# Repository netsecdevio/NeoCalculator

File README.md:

<div align="center">

<br>

# 🔢 NumOS

### Open-Source Scientific Graphing Calculator OS

**ESP32-S3 N16R8 · ILI9341 IPS 320×240 · LVGL 9.x · CAS Engine · Natural Display V.P.A.M.**

<br>

**[🚀 Join the Hardware Waitlist here](https://neocalculator.tech)** to get notified when PCB beta units drop.

---

</div>

> **Youth Hacking 4 Freedom 2026 submission:** see [`YH4F_SUBMISSION.md`](YH4F_SUBMISSION.md).
>
> **Demo video:** [youtu.be/IOTeKleOHQY](https://youtu.be/IOTeKleOHQY) — launcher, Calculation, natural-display math, and Grapher.

## Table of Contents

0. [Webpage](https://neocalculator.tech/)
1. [What is NumOS?](#what-is-numos)
2. [Key Features](#key-features)
3. [Photo Gallery](#photo-gallery)
4. [System Architecture](#system-architecture)
5. [CAS Engine](#CAS-engine)
6. [Hardware](#hardware)
7. [Quick Start](#quick-start)
8. [User Manual — EquationsApp](#user-manual--equationsapp)
9. [Project Structure](#project-structure)
10. [Build Stats](#build-stats)
11. [Critical Hardware Fixes](#critical-hardware-fixes)
12. [Project Status](#project-status)
13. [Technology Stack](#technology-stack)
14. [Comparison with Commercial Calculators](#comparison-with-commercial-calculators)
15. [Documentation](#documentation)
16. [Contributing](#contributing)

---

## What is NumOS?

**NumOS** is an open-source scientific and graphing calculator operating system built on the **ESP32-S3 N16R8** microcontroller (16 MB QIO runtime flash, DIO ROM boot header + 8 MB PSRAM OPI). The project aims to provide advanced features comparable to established scientific calculators, including symbolic mathematics, graphing, and natural display formatting.

*Working toward delivering a capable CAS experience for a ~€20 BOM as an open-source alternative in the educational calculator space.*

**NumOS delivers:**

- **Giac-backed CAS Engine** — Symbolic math implementation using Giac C++ via `src/math/giac/GiacBridge.cpp` for evaluation. Legacy CAS-S3 modules remain documented as historical milestones and optional local tooling.
- **Natural Display V.P.A.M.** — Formulae rendered as they appear on paper: real stacked fractions, radical symbols (√), genuine superscripts, 2D navigation with a structural smart cursor.
 - **Modern LVGL 9.x Interface** — Smooth transitions, animated splash screen, NumWorks-style launcher.
    Recent launcher refactor: the launcher now uses LVGL Flex `ROW_WRAP` (dynamic rows) with fixed card sizing
    instead of a static grid descriptor. See `docs/UI_CHANGES.md` for developer migration notes and
    `docs/fluid2d_plan.md` for an example app (Fluid2D) integrated into the new APPS[] schema.
- **Custom Numeric Math Engine** — Complete pipeline: Tokenizer → Shunting-Yard Parser → RPN Evaluator + Visual AST, implemented from scratch in C++17.
- **Modular App Architecture** — Each application is a self-contained module with explicit lifecycle (`begin/end/load/handleKey`), orchestrated by `SystemApp`.

---

## Key Features

| Feature | Description |
|:--------|:------------|
| **Giac CAS Backend** | *Experimental / in progress — not a validated CAS.* Symbolic evaluation through `GiacBridge` with UART parser/eval flow exercised on hardware. Milestones: `-DDOUBLEVAL`, 64 KB loop stack, real-style `complex_mode(false)` with preserved `i^2=-1` behavior |
| **Unified Calculus App** | *Experimental / still rough.* Symbolic $d/dx$ differentiation (17 rules) and numerical/symbolic $\int dx$ integration (Slagle heuristic: table lookup, linearity, u-substitution, integration by parts/LIATE), tab-based mode switching, automatic simplification, and step-by-step output |
| **EquationsApp** | *Experimental; the "steps" view is alpha.* Solves linear, quadratic, and 2×2 systems (linear + non-linear via Sylvester resultant) with step-by-step display |
| **Bridge Designer** | *Prototype.* Real-time structural bridge simulator with Verlet integration physics, stress analysis (green→red beam visualisation), snap-to-grid editor, wood/steel/cable materials, and truck/car load testing — PSRAM-backed, 60 Hz fixed timestep |
| **Particle Lab** | *Experimental.* Powder-Toy-class sandbox: 30+ materials (Sand, Water, Lava, LN2, Wire, Iron, Titan, C4, Clone), spark electronics with Joule heating, phase transitions, reaction matrix (Water+Lava=Stone+Steam), Bresenham line tool, material palette overlay, LittleFS save/load |
| **Settings App** | System-wide toggles for complex number output (ON/OFF), decimal precision selector (6/8/10/12 digits), and angle-mode display |
| **Natural Display** | Real fractions, radicals, exponents, 2D cursors — mathematical rendering as it appears on paper |
| **Graphing: y=f(x)** | Real-time function plotter with zoom, pan, and value table |
| **53 CAS Unit Tests** | CAS unit-test suite (Phases A–D), compile-time gated and off by default |
| **PSRAMAllocator** | CAS uses `PSRAMAllocator<T>` to isolate memory usage in the 8 MB PSRAM OPI |
| **Variables A–Z + Ans** | Persistent storage via LittleFS — 216 bytes in `/vars.dat` |
| **SerialBridge** | Full calculator control from PC via Serial Monitor without physical hardware |
| **SerialBridge Debug** | Immediate byte echo, 5-second heartbeat, 8-event circular buffer |

---

## Photo gallery

### Neural Network Simulator:

### Fluid 2D Simulator:

### Periodic Table (Chemistry App):

### Grapher App:

### Steps (Equations App) (WIP, still in development, Alpha):

### Calculus App:

### Probability (Gaussian Distribution):

### Python App:

### Bridge Designer:

### Circuit Simulator (Circuit Core, Alpha):

### Particle Lab (Powder Toy like):

### Optics Lab:

---

## System Architecture

```mermaid
flowchart TB
   subgraph esp[ESP32-S3 N16R8]
      main["main.cpp: setup() → PSRAM, TFT, LVGL, Splash, SystemApp; loop(): lv_timer_handler(), app.update(), serial.poll()"]
      system["SystemApp (Dispatcher)"]
      main --> system
   end

   subgraph apps[Applications]
      mm["MainMenu (LVGL)"]
      calc["CalculationApp (Natural VPAM, History)"]
      grapher["GrapherApp (y=f(x), Zoom & Pan)"]
      eq["EquationsApp (CAS)"]
      calculus["CalculusApp (d/dx, ∫dx)"]
      settings["SettingsApp"]
   end

   system --> mm
   system --> calc
   system --> grapher
   system --> eq
   system --> calculus
   system --> settings

   math["Math Engine: Tokenizer · Parser · Evaluator · ExprNode · VariableContext · EquationSolver"]
   procas["CAS Engine: CASInt · CASRational · SymExpr DAG · SymSimplify · SymDiff · SymIntegrate"]

   system --> math
   math --> procas

   display["Display Layer: DisplayDriver · LVGL flush DMA · ILI9341 @ 10 MHz"]
   input["Input Layer: KeyMatrix 5x10 · SerialBridge · LvglKeypad · LittleFS"]

   system --> display
   system --> input

   display -->|SPI @ 10 MHz| ili["ILI9341 IPS 3.2 in — 320x240 · 16 bpp"]
   ili -.-> esp
```

---

## CAS Engine

The **CAS** (Computer Algebra System) now uses **Giac C++ as the canonical symbolic backend**. The migration is routed through `src/math/giac/GiacBridge.cpp` and consumed by the UART command path in `src/input/SerialBridge.cpp`.

Legacy CAS-S3 internals documented below remain as historical milestones and optional local components, but symbolic truth for current backend flows comes from Giac.

### Giac Migration Milestones

- Big Switch complete: custom symbolic backend replaced by Giac as canonical CAS.
- Embedded numeric stabilization complete with `-DDOUBLEVAL`.
- Stack stabilization complete with `-DARDUINO_LOOP_STACK_SIZE=65536`.
- Real-style defaults complete: `complex_mode(false)` and preserved imaginary unit behavior (`i^2 = -1`).
- UART command path certified on hardware for `sum`, `int`, `solve`, and `simplify`.

### CAS Pipeline (Derivatives)

```mermaid
flowchart TB
   user["User input (CalculusApp): x^3 + sin(x)"]
   user --> me["Math Engine: Parser + Tokenizer"]
   me --> af["ASTFlattener: MathAST → SymExpr DAG"]
   af --> sd["SymDiff → d/dx: 3x^2 + cos(x)"]
   sd --> ss["SymSimplify (8-pass fixed-point)"]
   ss --> sea["SymExprToAST: SymExpr → MathAST (Natural Display)"]
   sea --> canvas["MathCanvas renders: 3x^2 + cos(x)"]
```

### CAS Pipeline (Integrals)

```mermaid
flowchart TB
   userInt["User input (CalculusApp, ∫dx mode): x · cos(x)"]
   userInt --> af2["ASTFlattener → SymExpr DAG"]
   af2 --> sint["SymIntegrate (Slagle): table → linearity → u-sub → parts (LIATE)"]
   sint --> ss2["SymSimplify"]
   ss2 --> conv["SymExprToAST::convertIntegral()"]
   conv --> canvas2["MathCanvas renders: x·sin(x) + cos(x) + C"]
```

### CAS Components

| Module | File | Responsibility |
|:-------|:-----|:---------------|
| `CASInt` | `cas/CASInt.h` | Hybrid BigInt: `int64_t` fast-path + `mbedtls_mpi` on overflow |
| `CASRational` | `cas/CASRational.h/.cpp` | Overflow-safe exact fraction (num/den with auto-GCD) |
| `PSRAMAllocator<T>` | `cas/PSRAMAllocator.h` | STL allocator → `ps_malloc`/`ps_free` for PSRAM |
| `SymExpr` DAG | `cas/SymExpr.h/.cpp` | Immutable symbolic tree with hash (`_hash`) and weight (`_weight`) |
| `ConsTable` | `cas/ConsTable.h` | PSRAM hash-consing table: deduplication of identical nodes |
| `SymExprArena` | `cas/SymExprArena.h` | PSRAM bump allocator (16 blocks × 64 KB) + integrated ConsTable |
| `ASTFlattener` | `cas/ASTFlattener.h/.cpp` | MathAST (VPAM) → SymExpr DAG with hash-consing |
| `SymDiff` | `cas/SymDiff.h/.cpp` | Symbolic differentiation: 17 rules (chain, product, quotient, trig, exp, log) |
| `SymIntegrate` | `cas/SymIntegrate.h/.cpp` | Slagle integration: table, linearity, u-substitution, parts (LIATE) |
| `SymSimplify` | `cas/SymSimplify.h/.cpp` | Multi-pass simplifier (8 iterations, fixed-point, trig/log/exp) |
| `SymPoly` | `cas/SymPoly.h/.cpp` | Univariable symbolic polynomial with `CASRational` coefficients |
| `SymPolyMulti` | `cas/SymPolyMulti.h/.cpp` | Multivariable polynomial + Sylvester resultant |
| `SingleSolver` | `cas/SingleSolver.h/.cpp` | Single-variable equation: linear / quadratic / Newton-Raphson |
| `SystemSolver` | `cas/SystemSolver.h/.cpp` | 2×2 system: Gaussian elimination + non-linear (resultant) |
| `OmniSolver` | `cas/OmniSolver.h/.cpp` | Analytic variable isolation: inverses, roots, trig |
| `HybridNewton` | `cas/HybridNewton.h/.cpp` | Newton-Raphson with symbolic Jacobian and 16-seed multi-start |
| `CASStepLogger` | `cas/CASStepLogger.h/.cpp` | `StepVec` in PSRAM — detailed steps (INFO/FORMULA/RESULT/ERROR) |
| `SymToAST` | `cas/SymToAST.h/.cpp` | Bridge: `SolveResult` → MathAST Natural Display |
| `SymExprToAST` | `cas/SymExprToAST.h/.cpp` | Bridge: `SymExpr` → MathAST. Includes `convertIntegral()` (+C) |

### CAS Tests — 53 Unit Tests

| Phase | Tests | Coverage |
|:------|:-----:|:---------|
| **A — Foundations** | 1–18 | `Rational`: add, subtract, multiply, divide, simplification. `SymPoly`: arithmetic, derivation, normalisation. |
| **B — ASTFlattener** | 19–32 | AST→SymPoly conversion for simple polynomials, constants, trig functions, powers. |
| **C — SingleSolver** | 33–44 | Linear (single solution), quadratic (2 real roots, repeated root, negative discriminant), steps. |
| **D — SystemSolver** | 45–53 | 2×2 determined system, indeterminate (infinite solutions), incompatible system. |

```ini
# platformio.ini — enable tests:
build_flags    = ... -DCAS_RUN_TESTS
build_src_filter = +<*> +<../tests/CASTest.cpp>
```

---

## Hardware

> ⚠️ **Alpha** PCB and enclosure design files (Rev A, not final — please don't order or print yet): see [`hardware/README.md`](hardware/README.md).

| Component | Specification |
|:----------|:-------------|
| **MCU** | ESP32-S3 N16R8 CAM — Dual-core Xtensa LX7 @ 240 MHz |
| **Flash** | 16 MB QIO (`default_16MB.csv`) |
| **PSRAM** | 8 MB OPI (`qio_opi` — critical to prevent boot panic) |
| **Display** | ILI9341 IPS TFT 3.2" — 320×240 px — SPI @ 10 MHz (verified) |
| **SPI Bus** | FSPI (SPI2): MOSI=13, SCLK=12, CS=10, DC=4, RST=5 |
| **Backlight** | GPIO 45 — hardwired to 3.3V (`pinMode(45, INPUT)`) |
| **Keyboard** | 5×10 matrix (Phase 7) — Rows OUTPUT: GPIO 1,2,41,42,40 · Cols INPUT_PULLUP: GPIO 6,7,8… |
| **Storage** | LittleFS on dedicated partition — persistent A–Z variables |
| **USB** | Native USB-CDC on S3 — 115 200 baud |

**Next physical milestone:** transition to the ESP32-P4 ("No-Radio") as the hardware path to Exam Mode compliance, meeting school regulations without locking down the software.

### Full Pinout

#### ILI9341 Display

| Signal | GPIO | Notes |
|:-------|:----:|:------|
| MOSI | 13 | FSPI Data In |
| SCLK | 12 | FSPI Clock |
| CS | 10 | Chip Select (active LOW) |
| DC | **4** | Data/Command |
| RST | **5** | Reset |
| BL | 45 | Hardwired to 3.3V — always INPUT |

#### 5×10 Keyboard Matrix (driver `Keyboard`, Phase 7)

| Row | GPIO | Role | Column | GPIO | Role |
|:----|:----:|:-----|:-------|:----:|:-----|
| ROW 0 | 1 | OUTPUT | COL 0 | 6 | INPUT_PULLUP |
| ROW 1 | 2 | OUTPUT | COL 1 | 7 | INPUT_PULLUP |
| ROW 2 | 41 | OUTPUT | COL 2 | 8 | INPUT_PULLUP |
| ROW 3 | 42 | OUTPUT | COL 3–9 | 3,15,16,17,18,21,47 | not yet wired |
| ROW 4 | 40 | OUTPUT | — | — | — |

> ✅ **GPIO 4/5 conflict resolved (2026-03-02)**: Keyboard columns C0 and C1 reassigned from GPIO 4/5 (`TFT_DC`/`TFT_RST`) to GPIO 6/7. The three currently wired columns use GPIO 6, 7, and 8 — no display conflict.

---

## Quick Start

### Requirements

- [PlatformIO IDE](https://platformio.org/install/ide?install=vscode) (VS Code extension)
- **PlatformIO Core CLI** (`pio`) for the command-line builds below — bundled with the
  IDE extension's own terminal, or install it standalone for a normal Terminal/shell
  (macOS: `brew install platformio`; any OS: `pip install -U platformio`). Verify with
  `pio --version`.
- USB drivers for ESP32-S3 (no external driver needed on Windows 11+)
- Python 3.x (PlatformIO installs it automatically)

### Build and Flash

```bash
git clone https://github.com/El-EnderJ/NeoCalculator.git
cd NeoCalculator

# Build only
pio run -e esp32s3_n16r8

# Build a validated production/recovery package
python scripts/esp32_boot.py package

# Application-only development upload
python scripts/esp32_boot.py flash-app --port <PORT>

# Open serial monitor (115 200 baud)
pio device monitor
```

### Run on Your PC — Desktop Emulator (no ESP32 required)

Want to try NumOS **without buying any hardware**? The SDL2 desktop emulator runs
the real UI and math code on your computer — no ESP32-S3 board needed:

```bash
pio --version                   # confirm the PlatformIO CLI is installed and on your PATH
pio run -e emulator_pc -t exec  # build AND open the emulator window (one step)
```

> **`-t exec` builds *and runs* it.** Plain `pio run -e emulator_pc` only
> **compiles** the emulator — it does **not** open a window. Add `-t exec` (or use
> the [run scripts](docs/emulator-sdl2-quickstart.md)) to actually launch it. macOS/
> Linux can also use `./scripts/run-emulator.sh`; Windows uses
> `./scripts/run-emulator-windows.ps1` (it also resolves `SDL2.dll`).

> The `esp32s3_*` targets above are **firmware builds for real hardware**;
> `emulator_pc` is the **desktop** target. A bare `pio run` (no `-e`) builds *every*
> environment, which is slower — pass `-e emulator_pc` to build only the emulator.

> **VS Code users:** to run the emulator, use **Terminal → Run Task… → “Run NumOS
> Emulator”** (or run the command above in a terminal). Do **not** press **Run/Debug
> (F5)** or pick **“PIO Debug”** / **“Electron Main”** — “PIO Debug” targets a real
> ESP32 over JTAG and fails without a board, and NumOS is not an Electron app. See
> [Build vs. Run vs. Debug](docs/emulator-sdl2-quickstart.md#build-vs-run-vs-debug-and-vs-code).

> **`command not found: pio` (macOS `zsh` / Linux)?** The PlatformIO **CLI** isn't on
> your PATH yet. The VS Code PlatformIO IDE extension bundles PlatformIO inside *its
> own* terminal — a normal Terminal/shell needs the standalone CLI. On **macOS**
> (Homebrew):
>
> ```bash
> brew install platformio        # PlatformIO CLI
> brew install sdl2 pkg-config   # SDL2 desktop dependency for the emulator
> pio --version                  # confirm the CLI is now on your PATH
> pio run -e emulator_pc
> ```

Full setup (including installing SDL2 on Windows/Linux/macOS) and a troubleshooting
guide live in the
**[SDL2 Desktop Emulator Quickstart](docs/emulator-sdl2-quickstart.md)** — start
there if your `esp32s3_*` builds pass but `emulator_pc` fails (or if `pio` is
"command not found").

### Serial Keyboard Control (SerialBridge)

With the Serial Monitor open, type characters to control the calculator:

| Key | Action | | Key | Action |
|:---:|:-------|-|:---:|:-------|
| `w` | ↑ Up | | `z` | ENTER / Confirm |
| `s` | ↓ Down | | `x` | DEL / Delete |
| `a` | ← Left | | `c` | AC / Clear |
| `d` | → Right | | `h` | MODE / Return to menu |
| `0`–`9` | Digits | | `+-*/^.()` | Operators |
| `S` | SHIFT | | `r` | √ SQRT |
| `t` | sin | | `g` | GRAPH |
| `e` | `=` (equation) | | `R` | SHOW STEPS |

> **Note**: lowercase `s` = DOWN; uppercase `S` = SHIFT. Disable CapsLock before use.

---

## User Manual — EquationsApp

The **EquationsApp** solves single-variable polynomial equations and 2×2 systems (linear and non-linear), displaying complete solution steps via the CAS engine.

### Access

1. From the Launcher, select **Equations** with ↑↓ and press ENTER.
2. The mode-selection screen appears.

### Mode 1: Single-Variable Equation

1. Select **Equation (1 var)** with ↑↓ and press ENTER.
2. The editor opens. Type your equation with the `=` sign:
   - `x^2 - 5x + 6 = 0`  →  x₁=2, x₂=3
   - `2x + 3 = 7`  →  x=2
   - `x^2 = -1`  →  no real solution (Δ < 0)
3. Press **ENTER** to solve.
4. The result screen shows:
   - **Linear**: a single solution `x = value`
   - **Quadratic**: discriminant Δ and up to 2 solutions `x₁`, `x₂`
   - **No real solution**: negative discriminant message
5. Press **SHOW STEPS** (`R`) to view detailed steps:
   - Normalised equation
   - Discriminant value Δ = b² − 4ac
   - Quadratic formula applied
   - Computed roots
6. Press **MODE** (`h`) to return to the main menu.

### Mode 2: 2×2 System

1. Select **System (2×2)** and press ENTER.
2. Two fields appear: **Eq 1** and **Eq 2**.
   - Type the first equation in `x` and `y`, press ENTER.
   - Type the second equation, press ENTER.
   - Example: `2x + y = 5` / `x - y = 1`  →  x=2, y=1
3. Press **ENTER** to solve. Displays `x = value, y = value`.
4. Press **SHOW STEPS** to view the full Gaussian elimination.
5. Press **MODE** to return.

### EquationsApp Keys

| Key | Action |
|:----|:-------|
| ↑ ↓ ← → | Navigate selection / cursor in editor |
| ENTER | Confirm mode / Solve equation |
| DEL | Delete character |
| AC | Clear field |
| SHOW STEPS | View detailed steps (from result screen) |
| MODE | Return to main menu |

---

## Project Structure

```
numOS/
├── src/
│   ├── main.cpp                      # Arduino entry point (setup/loop)
│   ├── SystemApp.cpp/.h              # Central orchestrator and LVGL launcher
│   ├── Config.h                      # Global ESP32-S3 pinout
│   ├── lv_conf.h                     # LVGL 9.x configuration
│   ├── HardwareTest.cpp              # Interactive keyboard test (inline)
│   ├── apps/
│   │   ├── CalculationApp.cpp/.h     # Natural V.P.A.M. calculator
│   │   ├── GrapherApp.cpp/.h         # y=f(x) graphing plotter
│   │   ├── EquationsApp.cpp/.h       # CAS — Equation solver
│   │   ├── CalculusApp.cpp/.h        # CAS — Unified symbolic derivatives + integrals
│   │   ├── BridgeDesignerApp.cpp/.h  # Bridge structural simulator (Verlet physics)
│   │   ├── CircuitCoreApp.cpp/.h    # Circuit simulator (MNA, 30 components)
│   │   ├── Fluid2DApp.cpp/.h        # 2D fluid dynamics (Navier-Stokes)
│   │   ├── ParticleLabApp.cpp/.h    # Powder-Toy sandbox (30+ materials, electronics)
│   │   ├── ParticleEngine.cpp/.h    # Cellular automata engine (LUT, spark cycle)
│   │   └── SettingsApp.cpp/.h        # Settings: complex roots, precision, angle mode
│   ├── display/
│   │   └── DisplayDriver.cpp/.h      # TFT_eSPI FSPI + LVGL init + DMA flush
│   ├── input/
│   │   ├── KeyCodes.h                # KeyCode enum (48 keys)
│   │   ├── KeyMatrix.cpp/.h          # 5×10 hardware driver with debounce
│   │   ├── SerialBridge.cpp/.h       # Virtual keyboard via Serial
│   │   └── LvglKeypad.cpp/.h         # LVGL indev keypad adapter
│   ├── math/
│   │   ├── Tokenizer.cpp/.h          # Lexical analyser
│   │   ├── Parser.cpp/.h             # Shunting-Yard → RPN / Visual AST
│   │   ├── Evaluator.cpp/.h          # Numerical RPN evaluator
│   │   ├── ExprNode.h                # Expression tree (Natural Display)
│   │   ├── MathAST.h                 # V.P.A.M. tree: NodeRow/NodeFrac/NodePow…
│   │   ├── CursorController.h/.cpp   # MathAST editing cursor
│   │   ├── EquationSolver.cpp/.h     # Numerical Newton-Raphson
│   │   ├── VariableContext.cpp/.h    # Variables A–Z + Ans
│   │   ├── VariableManager.h/.cpp    # Persistent ExactVal storage
│   │   ├── StepLogger.cpp/.h         # Parser step logger
│   │   └── cas/                      # ★ Complete CAS Engine
│   │       ├── CASInt.h              # Hybrid BigInt (int64 + mbedtls_mpi)
│   │       ├── CASRational.h/.cpp    # Overflow-safe exact fraction
│   │       ├── ConsTable.h           # Hash-consing PSRAM (dedup)
│   │       ├── PSRAMAllocator.h      # STL allocator for PSRAM OPI
│   │       ├── SymExpr.h/.cpp        # Immutable DAG with hash + weight
│   │       ├── SymExprArena.h        # Bump allocator + ConsTable
│   │       ├── SymDiff.h/.cpp        # Symbolic differentiation (17 rules)
│   │       ├── SymIntegrate.h/.cpp   # Slagle integration (table/u-sub/parts)
│   │       ├── SymSimplify.h/.cpp    # Fixed-point simplifier (8 passes)
│   │       ├── SymPoly.h/.cpp        # Univariable symbolic polynomial
│   │       ├── SymPolyMulti.h/.cpp   # Multivariable polynomial + resultant
│   │       ├── ASTFlattener.h/.cpp   # MathAST → SymExpr DAG
│   │       ├── SingleSolver.h/.cpp   # Analytic linear + quadratic solver
│   │       ├── SystemSolver.h/.cpp   # 2×2 system (linear + NL resultant)
│   │       ├── OmniSolver.h/.cpp     # Analytic variable isolation
│   │       ├── HybridNewton.h/.cpp   # Newton-Raphson with symbolic Jacobian
│   │       ├── CASStepLogger.h/.cpp  # Steps in PSRAM (StepVec)
│   │       ├── SymToAST.h/.cpp       # SolveResult → visual MathAST
│   │       └── SymExprToAST.h/.cpp   # SymExpr → MathAST (+C, ∫)
│   └── ui/
│       ├── MainMenu.cpp/.h           # LVGL launcher grid 3×N
│       ├── MathRenderer.h/.cpp       # 2D MathCanvas renderer
│       ├── StatusBar.h/.cpp          # LVGL status bar
│       ├── GraphView.cpp/.h          # Graph widget
│       ├── Icons.h                   # App icon bitmaps
│       └── Theme.h                   # Colour palette and UI constants
├── tests/
│   ├── CASTest.h/.cpp                # CAS unit tests
│   ├── HardwareTest.cpp              # TFT + physical keyboard test
│   └── TokenizerTest_temp.cpp        # Tokenizer test
├── docs/
│   ├── CAS_UPGRADE_ROADMAP.md        # ★ CAS roadmap (6 phases, complete)
│   ├── ROADMAP.md                    # Phase history + future plan
│   ├── PROJECT_BIBLE.md              # Master software architecture
│   ├── MATH_ENGINE.md                # Math engine + CAS in detail
│   ├── HARDWARE.md                   # ESP32-S3 pinout, wiring, and bring-up
│   ├── CONSTRUCTION.md               # Physical assembly guide
│   └── DIMENSIONES_DISEÑO.md         # 3D chassis specifications
├── platformio.ini                    # PlatformIO configuration
├── wokwi.toml                        # Wokwi simulator (optional)
└── diagram.json                      # Wokwi circuit diagram
```

---

## Build Stats

> Compiled with `pio run -e esp32s3_n16r8` in **production** mode (CAS tests disabled)

| Resource | Used | Total | Percentage |
|:---------|-----:|------:|:----------:|
| **RAM** (data + bss) | 97 192 B | 327 680 B | **29.7 %** |
| **Flash** (program storage) | 1 518 269 B | 6 553 600 B | **23.2 %** |

**Flash saved vs test mode:** −39 444 B when deactivating `-DCAS_RUN_TESTS`.

To enable or disable CAS tests, edit `platformio.ini`:

```ini
; ---- Production mode (default) ----
; -DCAS_RUN_TESTS          ← commented out

; ---- Test mode — uncomment these two lines ----
; -DCAS_RUN_TESTS
; +<../tests/CASTest.cpp>  ← in build_src_filter
```

---

## Critical Hardware Fixes

Issues discovered and resolved during bring-up. **Essential** for any fork or new build:

| # | Problem | Symptom | Solution |
|:-:|:--------|:--------|:---------|
| **①** | Flash/PSRAM mode mismatch | ROM watchdog or PSRAM boot panic | DIO ROM header + QIO second stage + `memory_type = qio_opi` |
| **②** | SPI StoreProhibited | Crash in `TFT_eSPI::begin()` at address `0x10` | `-DUSE_FSPI_PORT` → `SPI_PORT=2` → `REG_SPI_BASE(2)=0x60024000` |
| **③** | Display noise | Horizontal lines and visual artefacts | Reduce SPI to 10 MHz: `-DSPI_FREQUENCY=10000000` |
| **④** | LVGL black screen | `lv_timer_handler()` invokes flush but no image appears | Buffers via `heap_caps_malloc(MALLOC_CAP_DMA\|MALLOC_CAP_8BIT)` — **never** `ps_malloc` |
| **⑤** | GPIO 45 BL short | Display stops responding on backlight init | `pinMode(45, INPUT)` — the pin is hardwired to 3.3V |
| **⑥** | Serial CDC lost | Output invisible in Serial Monitor on connect | `while(!Serial && millis()-t0 < 3000)` + `monitor_rts=0` in platformio.ini |

---

## Project Status

| Phase | Description | Status |
|:------|:------------|:------:|
| **Phase 1** | Math Engine — Tokenizer, Shunting-Yard Parser, RPN Evaluator, ExprNode, VariableContext | ✅ Implemented |
| **Phase 2** | Natural Display V.P.A.M. — fractions, radicals, exponents, smart 2D cursor | ✅ Implemented |
| **Phase 3** | Launcher 3.0, SerialBridge, CalculationApp history, GrapherApp zoom/pan | ✅ Implemented |
| **Phase 4** | LVGL 9.x — ESP32-S3 HW bring-up, DMA, animated splash screen, icon launcher | ✅ Implemented |
| **Phase 5** | CAS-Lite Engine (SymPoly, SingleSolver, SystemSolver, 53 tests) + EquationsApp UI (legacy milestone) | ✅ Implemented |
| **CAS** | CAS-S3 internal milestones: BigNum, hash-consed DAG, SymDiff 17 rules, SymIntegrate Slagle, SymSimplify 8-pass, OmniSolver | ✅ **Implemented** |
| **Giac Migration** | Giac integration: GiacBridge, UART parser/eval flow, `-DDOUBLEVAL`, 64 KB loop stack, real-mode defaults with `i` preserved | ✅ **Implemented** |
| **Phase 6** | Statistics, Regression, Sequences, Probability, Matrices, Bridge Designer (Prototype) | 🟡 **In Development** |
| **Simulations** | ParticleLab (30+ materials, electronics), CircuitCore (SPICE), Fluid2D (Navier-Stokes) (Experimental) | 🟡 **In Development** |
| **Phase 7** | Complex numbers, base conversions | 🔲 Planned |
| **Phase 8** | Physical keyboard (prototype stage), custom PCB, rechargeable battery, 3D enclosure, WiFi OTA | 🔲 Planned |

---

## Technology Stack

| Layer | Technology | Version |
|:------|:-----------|:-------:|
| **MCU Framework** | Arduino on ESP-IDF 5.x | PlatformIO espressif32 6.12.0 |
| **UI / Graphics** | LVGL | 9.5.0 |
| **TFT Driver** | TFT_eSPI | 2.5.43 |
| **Filesystem** | LittleFS | ESP-IDF built-in |
| **Language** | C++17 | lambdas, `std::function`, `std::unique_ptr` |
| **CAS Memory** | PSRAMAllocator STL custom | PSRAM OPI 8 MB |
| **Build System** | PlatformIO | 6.12.0 |
| **Simulation** | Wokwi | wokwi.toml |

---

## Comparison with Commercial Calculators

| Feature | **NumOS** | NumWorks | TI-84 Plus CE | HP Prime G2 |
|:--------|:---------:|:--------:|:-------------:|:-----------:|
| Open Source | ✅ GPL-3.0-or-later | ✅ Source-available | ❌ | ❌ |
| Natural Display | ✅ | ✅ | ✅ | ✅ |
| Symbolic CAS | 🟡 Giac | ✅ SymPy | ❌ | ✅ |
| Symbolic derivatives | 🟡 | ✅ | ❌ | ✅ |
| Symbolic integrals | 🟡 | ✅ | ❌ | ✅ |
| Solution steps | 🟡 | ❌ | ❌ | ✅ |
| Colour graphing | ✅ | ✅ | ✅ | ✅ |
| Multi-function graphing | 🔲 | ✅ | ✅ | ✅ |
| Statistics & Regression | 🟡 | ✅ | ✅ | ✅ |
| Matrices | 🔲 | ✅ | ✅ | ✅ |
| Complex numbers | 🔲 | ✅ | ✅ | ✅ |
| Scripting / Python | 🟡 NeoLanguage + Python | ✅ | ✅ TI-BASIC | ✅ HP PPL |
| WiFi / Connectivity | 🔲 | ✅ | ❌ | ❌ |
| Rechargeable battery | 🔲 | ✅ | ❌ | ✅ |
| Estimated HW cost | **~€15-25** | €79 | €149 | €179 |
| Platform | ESP32-S3 | STM32F730 | Zilog eZ80 | ARM Cortex-A7 |

> 📐 NumOS is developing CAS capabilities and cost-effectiveness as an open-source alternative, working toward feature parity with established commercial calculators.
>
> **Legend:** ✅ = working today · 🟡 = experimental / in progress · 🔲 = planned. See [`YH4F_SUBMISSION.md`](YH4F_SUBMISSION.md) for the honest current status of each feature.

---

## Documentation

| Document | Description |
|:---------|:------------|
| [ROADMAP.md](docs/ROADMAP.md) | Complete phase history, milestones, and detailed future plan |
| [PROJECT_BIBLE.md](docs/PROJECT_BIBLE.md) | Master architecture, modules, code conventions, and development guides |
| [CAS_UPGRADE_ROADMAP.md](docs/CAS_UPGRADE_ROADMAP.md) | Full roadmap for the 6-phase CAS upgrade |
| [MATH_ENGINE.md](docs/MATH_ENGINE.md) | Math engine + CAS: design, algorithms, pipeline, and examples |
| [HARDWARE.md](docs/HARDWARE.md) | ESP32-S3 pinout, complete wiring, critical bugs, and bring-up notes |
| [ESP32_BOOT_FLASHING.md](docs/ESP32_BOOT_FLASHING.md) | Authoritative development upload, provisioning, and recovery workflow |
| [CONSTRUCTION.md](docs/CONSTRUCTION.md) | Physical assembly guide, 3D printing, and hardware testing |
| [DIMENSIONES_DISEÑO.md](docs/DIMENSIONES_DISEÑO.md) | Dimensional specifications for the 3D chassis |

---

## Support the Project ☕

The EV grant graciously covers the core hardware prototyping. However, I have set a **€500 goal** on Ko-fi to fund the crucial **"invisible"** infrastructure of NumOS. 

Your support directly funds:
1. ** AI & Dev Tools:** Subscriptions for Claude/Copilot to accelerate C++ optimization and the Giac engine porting.
2. **Digital Presence:** Domain hosting (`neocalculator.tech` / `numos.org`) and backend web services.
3. **Beta Shipping:** Sending physical beta units to expert contributors globally to accelerate community development.

Every contribution keeps me focused on the mission and ensures NumOS stays independent and open-source.

---

## Contributing

NumOS is an open-source project in active development that welcomes community contributions. The software is currently in prototype/alpha stage and validates features on the current ESP32-S3 N16R8 hardware platform.

1. **Fork** the repository.
2. Create a branch: `git checkout -b feature/descriptive-name`
3. Follow the [code conventions](docs/PROJECT_BIBLE.md#guia-de-estilo) of the project.
4. Verify the build passes: `pio run -e esp32s3_n16r8`
5. If you add math logic, include tests in `tests/`.
6. Open a **Pull Request** with a clear description of your changes.

### Areas Where Help Is Most Needed

| Module | Description |
|:-------|:------------|
| **Custom PCB** | KiCad schematic with integrated ESP32-S3 + TP4056 charger |
| **Sequences App** | Arithmetic and geometric sequences, Nth term, partial sums |
| **Settings App** | ~~Angle mode DEG/RAD/GRA, brightness, factory reset~~ ✅ Done, remaining: brightness PWM, factory reset |
| **Advanced CAS** | ~~Symbolic derivatives and integrals~~ ✅ Done, remaining: definite integrals, series |
| **Better UI/UX** | General improvement on UI and UX for real product release |
| **Matrices** | Matrix editor, determinant, inverse, multiplication |
| **Physical keyboard** | ✅ GPIO 4/5 conflict resolved — `Keyboard` driver 5×10 implemented (Phase 7) |

---

<sub>*This project was developed with AI assistance (Claude/Copilot) for code generation, guided by the author's systems architecture decisions. All design choices like DAG structure, memory management, parser design, were made and validated by the author.*</sub>

## License & Intellectual Property

### Software (Firmware)

NumOS-authored software carrying the project notice is offered under
**GPL-3.0-or-later**; see [`LICENSE-SOFTWARE`](LICENSE-SOFTWARE). The repository
also contains separately licensed third-party components and generated font
data. The licence-history qualification is recorded in
[`docs/LICENSING_AUDIT_2026.md`](docs/LICENSING_AUDIT_2026.md). In particular,
the modified Giac/KhiCAS snapshot remains
GPL-3.0-or-later, while Montserrat and STIX Two Math font software and their
font-derived data remain under OFL-1.1.

See [`LICENSE.md`](LICENSE.md),
[`THIRD_PARTY_NOTICES.md`](THIRD_PARTY_NOTICES.md), and
[`lib/giac/NUMOS_CHANGES.md`](lib/giac/NUMOS_CHANGES.md) for the precise
component boundaries, provenance, and modification record.

### Hardware & Industrial Design

The hardware architecture of the **NeoCalculator**, including but not limited to:
* PCB Schematics and Layouts (KiCad files, Gerbers).
* Industrial Design and 3D Models (STL, STEP, CAD files).
* The "Exam Key" security architecture.

Is licensed under the **CERN Open Hardware Licence Version 2 - Strongly Reciprocal (CERN-OHL-S v2)**. 

We believe that hardware accessibility is crucial for education. Under this license, anyone is free to study, modify, manufacture, and distribute the physical calculator. 

**The Reciprocal Rule:** If you modify these designs and distribute or sell the resulting hardware, you **must** release your modified source files under this exact same CERN-OHL-S v2 license, ensuring the hardware ecosystem remains open and accessible forever. 

---

<div align="center">

*Built with ❤️ and a lot of C++17*

**NumOS, An open-source graphing calculator for ESP32-S3**

*Last updated: June 2026*

<div align="center">

</div>

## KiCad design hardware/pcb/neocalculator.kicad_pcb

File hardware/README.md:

# NeoCalculator hardware

> ⚠️ **Alpha hardware — not final. Please don't order PCBs or print enclosures yet.** This is an early revision published for transparency and review. The schematic, board layout, parts and enclosure are still changing and the next revision may not be compatible with this one. If you build it anyway, you do so at your own risk and cost.

| | |
|:--|:--|
| **Revision** | Rev A (alpha) |
| **Published** | 2026-11-02 |
| **Firmware at time of publication** | NumOS `ab40177` |

## Contents

### `pcb/` — main board

Two-layer board, 76 × 156 mm: ESP32-S3-WROOM-1U-N16R8, TP4056 Li-ion charger with DW01 + 8205A protection, RT6150A buck-boost regulator, USB-C, 40-pin FPC display connector, and a 5 × 10 key matrix (50 keys, one 1N4148 diode per key).

| File | What it is | Opens with |
|:-----|:-----------|:-----------|
| `neocalculator.kicad_sch` | Schematic source | KiCad 10.0 or later |
| `neocalculator.kicad_pcb` | Board layout source | KiCad 10.0 or later |
| `neocalculator-schematic.pdf` | Schematic export | Any PDF viewer |
| `neocalculator-board-outline.pdf` | Board outline / placement drawing with enclosure dimensions | Any PDF viewer |
| `neocalculator-gerbers.zip` | Gerbers + drill files, ready to upload to JLCPCB | Any Gerber viewer |
| `neocalculator-bom.xlsx` | Bill of materials with JLCPCB/LCSC part numbers | Excel, LibreOffice |
| `neocalculator-cpl.xlsx` | Pick-and-place (component placement list) | Excel, LibreOffice |

The display (Z320IT008-D, connected over SPI) and the Li-ion battery are off-board parts and are not in the BOM.

The schematic still shows the original USB-C connector (`type-c 16pin 2md(073)`); the layout, Gerbers and BOM use the HANBO MC-121-L124 that replaced it during layout. The BOM is the reference for the fitted part.

### `enclosure/` — 3D-printed case

Body 84 × 172 mm. Published as STL meshes (CAD sources are not included in this release).

| File | Part |
|:-----|:-----|
| `case-top.stl` | Case top |
| `case-bottom.stl` | Case bottom |
| `key.stl` | Key top (print 50, plus spares) |
| `switch-slider.stl` | Power switch slider |
| `display-shim.stl` | Display shim |
| `ASSEMBLY.md` | Print settings and assembly steps |

### `keyboard/` — keypad map

Machine-readable keypad layout and the generated key map used by the firmware's production keypad pipeline.

## License

The NeoCalculator hardware design files in this directory are licensed under the **CERN Open Hardware Licence Version 2 — Strongly Reciprocal (CERN-OHL-S-2.0)**. The full text is in [`LICENSE-HARDWARE`](../LICENSE-HARDWARE).

The NumOS firmware is licensed separately; see [`LICENSE.md`](../LICENSE.md).

## Credits

- **PCB design:** El-EnderJ
- **Enclosure design:** Charles Baynes

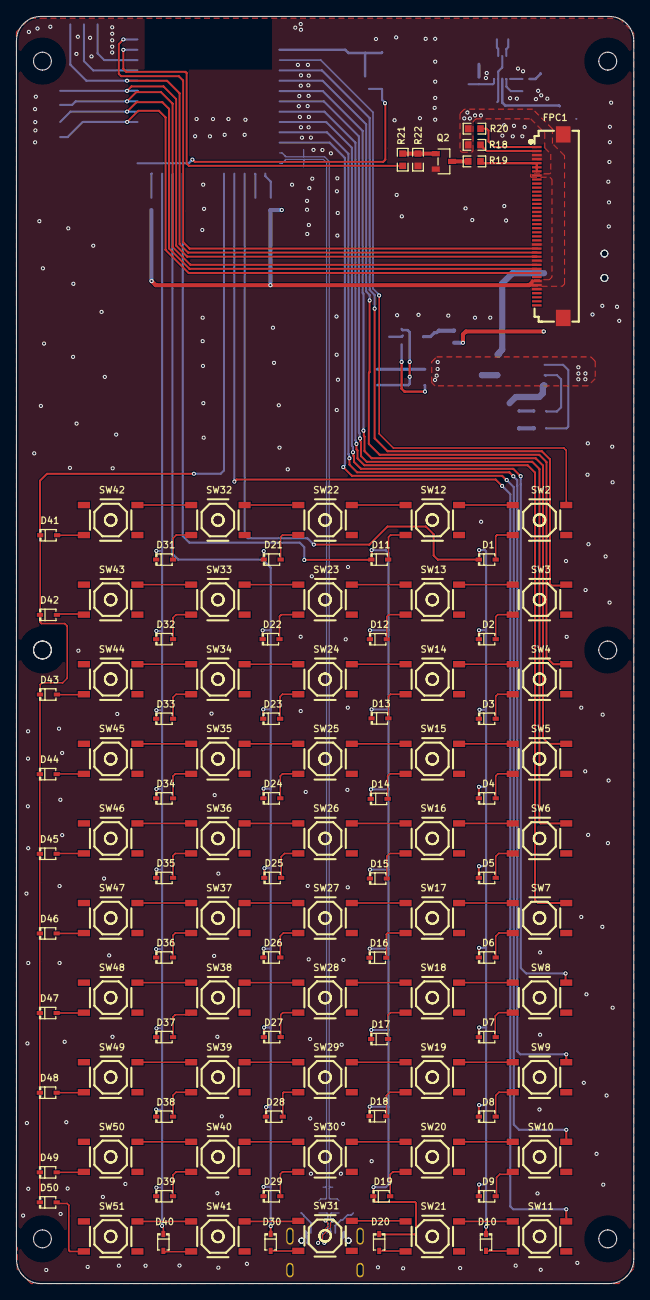
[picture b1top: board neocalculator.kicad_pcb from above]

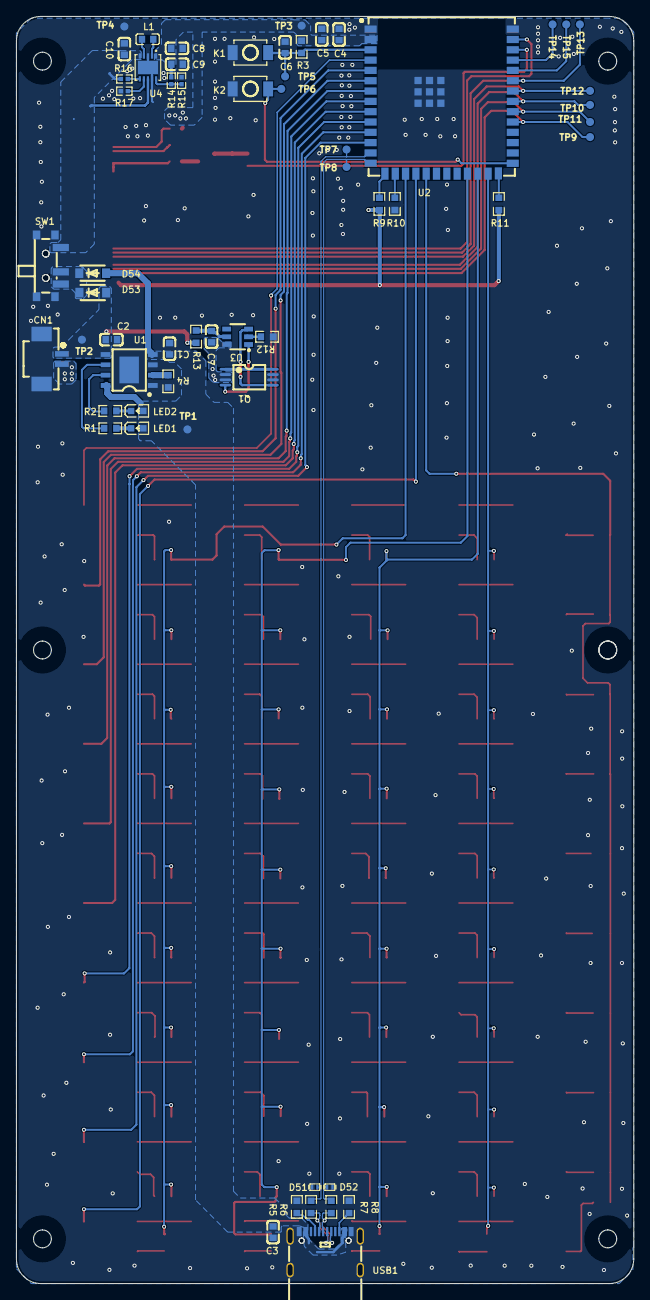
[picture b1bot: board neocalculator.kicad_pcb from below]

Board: 2 copper layers, 76.0 x 156.0 mm, 166 parts (59 on the bottom side), 152 nets.

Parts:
C1, C2: 10uF; C0603
C3: 0.1uF; C0603
C4: 22uF/16V; C0603
C5, C6: 104; C0603
C7: 100nF; C0603
C8, C9, C10: 10UF; C0603
CN1: ZX-MX1.25-2PWT; CONN-SMD_2P-P1.25_MEGASTAR_ZX-MX1.25-2PWT
D1, D2, D3, D4, D5, D6, D7, D8, D9, D10, D11, D12, D13, D14, D15, D16, D17, D18, D19, D20, D21, D22, D23, D24, D25, D26, D27, D28, D29, D30, D31, D32, D33, D34, D35, D36, D37, D38, D39, D40, D41, D42, D43, D44, D45, D46, D47, D48, D49, D50: 1n4148ws_c7420319; SOD-323_L1.7-W1.3-LS2.5-FD
D51, D52: h5vl10b; SOD-882_L1.0-W0.6-BI
D53, D54: ss14l; SOD-123F_L2.8-W1.8-LS3.7-RD
FPC1: fpc-05fb-40ph20; FPC-SMD_40P-P0.50_XUNPU_FPC-05FB-40PH20
K1, K2: RST; SW-SMD_L3.9-W3.0-P4.45
L1: 2.2uH; L0603
LED1: XL-1608PGC-06; LED0603-RD_RED
LED2: XL-1608SURC-06; LED0603-RD_RED
Q1: 8205A; TSSOP-8_L4.4-W3.0-P0.65-LS6.4-BL
Q2: 8050; SOT-23-3_L2.9-W1.3-P1.90-LS2.4-BR
R1, R2, R12, R18, R20: 1K; R0603
R3, R9, R10, R11, R22: 10k; R0603
R4: 2.4K; R0603
R5, R8: 5.1K; R0603
R6, R7: 0R; R0603
R13: 100R; R0603
R14: 487K; R0402
R15: 86.6K; R0402
R16, R17: 100K; R0402
R19: 10R; R0603
R21: 1k; R0603
SW1: mk-12c02-g020; SW-SMD_MK-12C02-G020
SW2, SW3, SW4, SW5, SW6, SW7, SW8, SW9, SW10, SW11, SW12, SW13, SW14, SW15, SW16, SW17, SW18, SW19, SW20, SW21, SW22, SW23, SW24, SW25, SW26, SW27, SW28, SW29, SW30, SW31, SW32, SW33, SW34, SW35, SW36, SW37, SW38, SW39, SW40, SW41, SW42, SW43, SW44, SW45, SW46, SW47, SW48, SW49, SW50, SW51: ts-1187s-20; SW-SMD_4P-L5.1-W5.1-P3.70-LS6.4
TP1, TP2, TP3, TP4, TP5, TP6, TP7, TP8, TP9, TP10, TP11, TP12, TP13, TP14, TP15: Test; TP
U1: TP4056; ESOP-8_L4.9-W3.9-P1.27-LS6.0-BL-EP
U2: esp32-s3-wroom-1u-n16r8; WIRELM-SMD_ESP32-S3-WROOM-1U
U3: DW01HA; SOT-23-6_L2.9-W1.6-P0.95-LS2.8-BR
U4: RT6150AGQW; WDFN-10_L3.0-W3.0-P0.50-BL-EP
USB1: MC-121-L124; USB-C-SMD_HANBO_MC-121-L124

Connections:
BOOT: K2.1, TP6.1, U2.27
CSX/SPI_CS: FPC1.9, TP9.1, U2.31
DCX/SPI_SCLK: FPC1.10, TP10.1, U2.32
G2: Q1.5, U3.3
GND: C1.1, C2.2, C3.2, C4.1, C5.1, C6.2, C8.1, C9.1, C10.2, CN1.3, CN1.4, D51.2, D52.2, FPC1.5, FPC1.12, FPC1.16, FPC1.37, FPC1.38, FPC1.41, FPC1.42, K1.1, K2.2, Q1.6, Q1.7, Q2.2, R4.1, R5.2, R8.2, R10.2, R12.1, R15.1, R17.1, R22.2, SW1.4, SW1.5, SW1.6, SW1.7, TP4.1, U1.1, U1.3, U1.9, U2.1, U2.40, U2.41, U4.3, U4.9, U4.11, USB1.13, USB1.14, USB1.A1B12, USB1.B1A12
IM1: FPC1.39, R18.2
IM2: FPC1.40, R20.2
IO1: FPC1.15, U2.39
IO2: R21.2, U2.38
IO4: SW2.2, U2.4
IO5: SW3.2, U2.5
IO6: SW4.2, U2.6
IO7: SW5.2, U2.7
IO8: SW10.2, U2.12
IO9: D1.2, D2.2, D3.2, D4.2, D5.2, D6.2, D7.2, D8.2, D9.2, D10.2, U2.17
IO10: SW11.2, U2.18
IO11: D41.2, D42.2, D43.2, D44.2, D45.2, D46.2, D47.2, D48.2, D49.2, D50.2, U2.19
IO15: SW6.2, U2.8
IO16: SW7.2, U2.9
IO17: SW8.2, U2.10
IO18: SW9.2, U2.11
IO21: D11.2, D12.2, D13.2, D14.2, D15.2, D16.2, D17.2, D18.2, D19.2, D20.2, U2.23
IO40: FPC1.11, TP11.1, U2.33
IO41: FPC1.13, TP12.1, U2.34
IO42: FPC1.14, TP13.1, U2.35
IO47: D21.2, D22.2, D23.2, D24.2, D25.2, D26.2, D27.2, D28.2, D29.2, D30.2, U2.24
IO48: D31.2, D32.2, D33.2, D34.2, D35.2, D36.2, D37.2, D38.2, D39.2, D40.2, U2.25
LED_A: C4.2, C5.2, C8.2, C9.2, FPC1.6, FPC1.7, FPC1.33, R3.1, R9.1, R11.1, R14.2, R18.1, R20.1, TP3.1, U2.2, U4.1
LED_K: FPC1.34, FPC1.35, FPC1.36, R19.2
NetC7_1: C7.1, R13.1, U3.5
NetD1_1: D1.1, SW2.3
NetD2_1: D2.1, SW3.3
NetD3_1: D3.1, SW4.3
NetD4_1: D4.1, SW5.3
NetD5_1: D5.1, SW6.3
NetD6_1: D6.1, SW7.3
NetD7_1: D7.1, SW8.3
NetD8_1: D8.1, SW9.3
NetD9_1: D9.1, SW10.3
NetD10_1: D10.1, SW11.3
NetD11_1: D11.1, SW12.3
NetD12_1: D12.1, SW13.3
NetD13_1: D13.1, SW14.3
NetD14_1: D14.1, SW15.3
NetD15_1: D15.1, SW16.3
NetD16_1: D16.1, SW17.3
NetD17_1: D17.1, SW18.3
NetD18_1: D18.1, SW19.3
NetD19_1: D19.1, SW20.3
NetD20_1: D20.1, SW21.3
NetD21_1: D21.1, SW22.3
NetD22_1: D22.1, SW23.3
NetD23_1: D23.1, SW24.3
NetD24_1: D24.1, SW25.3
NetD25_1: D25.1, SW26.3
NetD26_1: D26.1, SW27.3
NetD27_1: D27.1, SW28.3
NetD28_1: D28.1, SW29.3
NetD29_1: D29.1, SW30.3
NetD30_1: D30.1, SW31.3
NetD31_1: D31.1, SW32.3
NetD32_1: D32.1, SW33.3
NetD33_1: D33.1, SW34.3
NetD34_1: D34.1, SW35.3
NetD35_1: D35.1, SW36.3
NetD36_1: D36.1, SW37.3
NetD37_1: D37.1, SW38.3
NetD38_1: D38.1, SW39.3
NetD39_1: D39.1, SW40.3
NetD40_1: D40.1, SW41.3
NetD41_1: D41.1, SW42.3
NetD42_1: D42.1, SW43.3
NetD43_1: D43.1, SW44.3
NetD44_1: D44.1, SW45.3
NetD45_1: D45.1, SW46.3
NetD46_1: D46.1, SW47.3
NetD47_1: D47.1, SW48.3
NetD48_1: D48.1, SW49.3
NetD49_1: D49.1, SW50.3
NetD50_1: D50.1, SW51.3
NetD53_1: D53.1, D54.1, SW1.2, SW1.3
NetL1_1: L1.1, U4.2
NetL1_2: L1.2, U4.4
NetLED1_1: LED1.1, R1.2
NetLED2_1: LED2.1, R2.2
NetQ1_1: Q1.1, Q1.8
NetQ1_4: Q1.4, U3.1
NetQ2_1: Q2.1, R21.1, R22.1
NetQ2_3: Q2.3, R19.1
NetR1_1: R1.1, U1.6
NetR2_1: R2.1, U1.7
NetR4_2: R4.2, U1.2
NetR5_1: R5.1, USB1.A5
NetR6_1: R6.1, USB1.A7, USB1.B7
NetR7_2: R7.2, USB1.A6, USB1.B6
NetR8_1: R8.1, USB1.B5
NetR9_2: R9.2, U2.15
NetR10_1: R10.1, U2.16
NetR11_2: R11.2, U2.26
NetR12_2: R12.2, U3.2
NetR14_1: R14.1, R15.2, U4.10
NetR16_2: R16.2, U4.6
NetR17_2: R17.2, U4.7
NetSW2_1: SW2.1, SW12.2
NetSW3_1: SW3.1, SW13.2
NetSW4_1: SW4.1, SW14.2
NetSW5_1: SW5.1, SW15.2
NetSW6_1: SW6.1, SW16.2
NetSW7_1: SW7.1, SW17.2
NetSW8_1: SW8.1, SW18.2
NetSW9_1: SW9.1, SW19.2
NetSW10_1: SW10.1, SW20.2
NetSW11_1: SW11.1, SW21.2
NetSW12_1: SW12.1, SW22.2
NetSW13_1: SW13.1, SW23.2
NetSW14_1: SW14.1, SW24.2
NetSW15_1: SW15.1, SW25.2
NetSW16_1: SW16.1, SW26.2
NetSW17_1: SW17.1, SW27.2
NetSW18_1: SW18.1, SW28.2
NetSW19_1: SW19.1, SW29.2
NetSW20_1: SW20.1, SW30.2
NetSW21_1: SW21.1, SW31.2
NetSW22_1: SW22.1, SW32.2
NetSW23_1: SW23.1, SW33.2
NetSW24_1: SW24.1, SW34.2
NetSW25_1: SW25.1, SW35.2
NetSW26_1: SW26.1, SW36.2
NetSW27_1: SW27.1, SW37.2
NetSW28_1: SW28.1, SW38.2
NetSW29_1: SW29.1, SW39.2
NetSW30_1: SW30.1, SW40.2
NetSW31_1: SW31.1, SW41.2
NetSW32_1: SW32.1, SW42.2
NetSW33_1: SW33.1, SW43.2
NetSW34_1: SW34.1, SW44.2
NetSW35_1: SW35.1, SW45.2
NetSW36_1: SW36.1, SW46.2
NetSW37_1: SW37.1, SW47.2
NetSW38_1: SW38.1, SW48.2
NetSW39_1: SW39.1, SW49.2
NetSW40_1: SW40.1, SW50.2
NetSW41_1: SW41.1, SW51.2
RESET: C6.1, K1.2, R3.2, TP5.1, U2.3
RXD: TP15.1, U2.36
TXD: TP14.1, U2.37
USB5V: C1.2, C3.1, D54.2, LED1.2, LED2.2, TP1.1, U1.4, U1.8, USB1.A4B9, USB1.B4A9
USB_D+: D52.1, R7.1, TP8.1, U2.14
USB_D-: D51.1, R6.2, TP7.1, U2.13
VBAT1+: C10.1, R16.1, SW1.1, U4.5, U4.8
VBAT+: C2.1, CN1.1, D53.2, R13.2, TP2.1, U1.5
VSS: C7.2, CN1.2, Q1.2, Q1.3, U3.6

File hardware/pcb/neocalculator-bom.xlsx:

Comment | Designator | Footprint | JLCPCB Part #（optional）
10uF / CL10A106MO8NQNC | C1,C2,C8,C9,C10 | C0603 | C92487
0.1uF / CL10B104KB8NNNC | C3,C5,C6,C7 | C0603 | C1591
22uF/16V / CL10A226MO7JZNC | C4 | C0603 | C2762594
ZX-MX1.25-2PWT | CN1 | CONN-SMD_2P-P1.25_MEGASTAR_ZX-MX1.25-2PWT | C7430468
1N4148WS | D1,D2,D3,D4,D5,D6,D7,D8,D9,D10,D11,D12,D13,D14,D15,D16,D17,D18,D19,D20,D21,D22,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 | SOD-323_L1.7-W1.3-LS2.5-FD | C7420319
H5VL10B | D51,D52 | SOD-882_L1.0-W0.6-BI | C7420372
SS14L | D53,D54 | SOD-123F_L2.8-W1.8-LS3.7-RD | C190475
FPC-05FB-40PH20 | FPC1 | FPC-SMD_40P-P0.50_XUNPU_FPC-05FB-40PH20 | C2856837
TS-1088-AR02016 | K1,K2 | SW-SMD_L3.9-W3.0-P4.45 | C720477
2.2uH / CMH160808B2R2MT | L1 | L0603 | C394950
XL-1608PGC-06 | LED1 | LED0603-RD_RED | C7371905
XL-1608SURC-06 | LED2 | LED0603-RD_RED | C965799
8205A | Q1 | TSSOP-8_L4.4-W3.0-P0.65-LS6.4-BL | C5148694
S8050 | Q2 | SOT-23-3_L2.9-W1.3-P1.90-LS2.4-BR | C20069125
1K / FRC0603F1001TS | R1,R2,R12,R18,R20,R21 | R0603 | C2907002
2.4K / FRC0603F2401TS | R4 | R0603 | C2907007
10K / RT0603BRD0710KL | R3,R9,R10,R11,R22 | R0603 | C95204
5.1K / FRC0603F5101TS | R5,R8 | R0603 | C2907044
0R / FRC0603F0000TS | R6,R7 | R0603 | C2906974
100R / RT0603BRD07100RL | R13 | R0603 | C122970
487K / ERJ2RKF4873X | R14 | R0402 | C416552
86.6K / ERJ2RKF8662X | R15 | R0402 | C2076776
100K / RT0402BRD07100KL | R16,R17 | R0402 | C852472
10R / FRC0603J100TS | R19 | R0603 | C2907091
MK-12C02-G020 | SW1 | SW-SMD_MK-12C02-G020 | C963206
TS-1187S-20 | SW2,SW3,SW4,SW5,SW6,SW7,SW8,SW9,SW10,SW11,SW12,SW13,SW14,SW15,SW16,SW17,SW18,SW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 | SW-SMD_4P-L5.1-W5.1-P3.70-LS6.4 | C19779060
TP4056 | U1 | ESOP-8_L4.9-W3.9-P1.27-LS6.0-BL-EP | C382139
ESP32-S3-WROOM-1U-N16R8 | U2 | WIRELM-SMD_ESP32-S3-WROOM-1U | C3013946
DW01HA. / FM | U3 | SOT-23-6_L2.9-W1.6-P0.95-LS2.8-BR | C49340405
RT6150AGQW | U4 | WDFN-10_L3.0-W3.0-P0.50-BL-EP | C147971
MC-121-L124 | USB1 | USB-C-SMD_HANBO_MC-121-L124 | C6332279

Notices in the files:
README.md:
License: GPL v3
